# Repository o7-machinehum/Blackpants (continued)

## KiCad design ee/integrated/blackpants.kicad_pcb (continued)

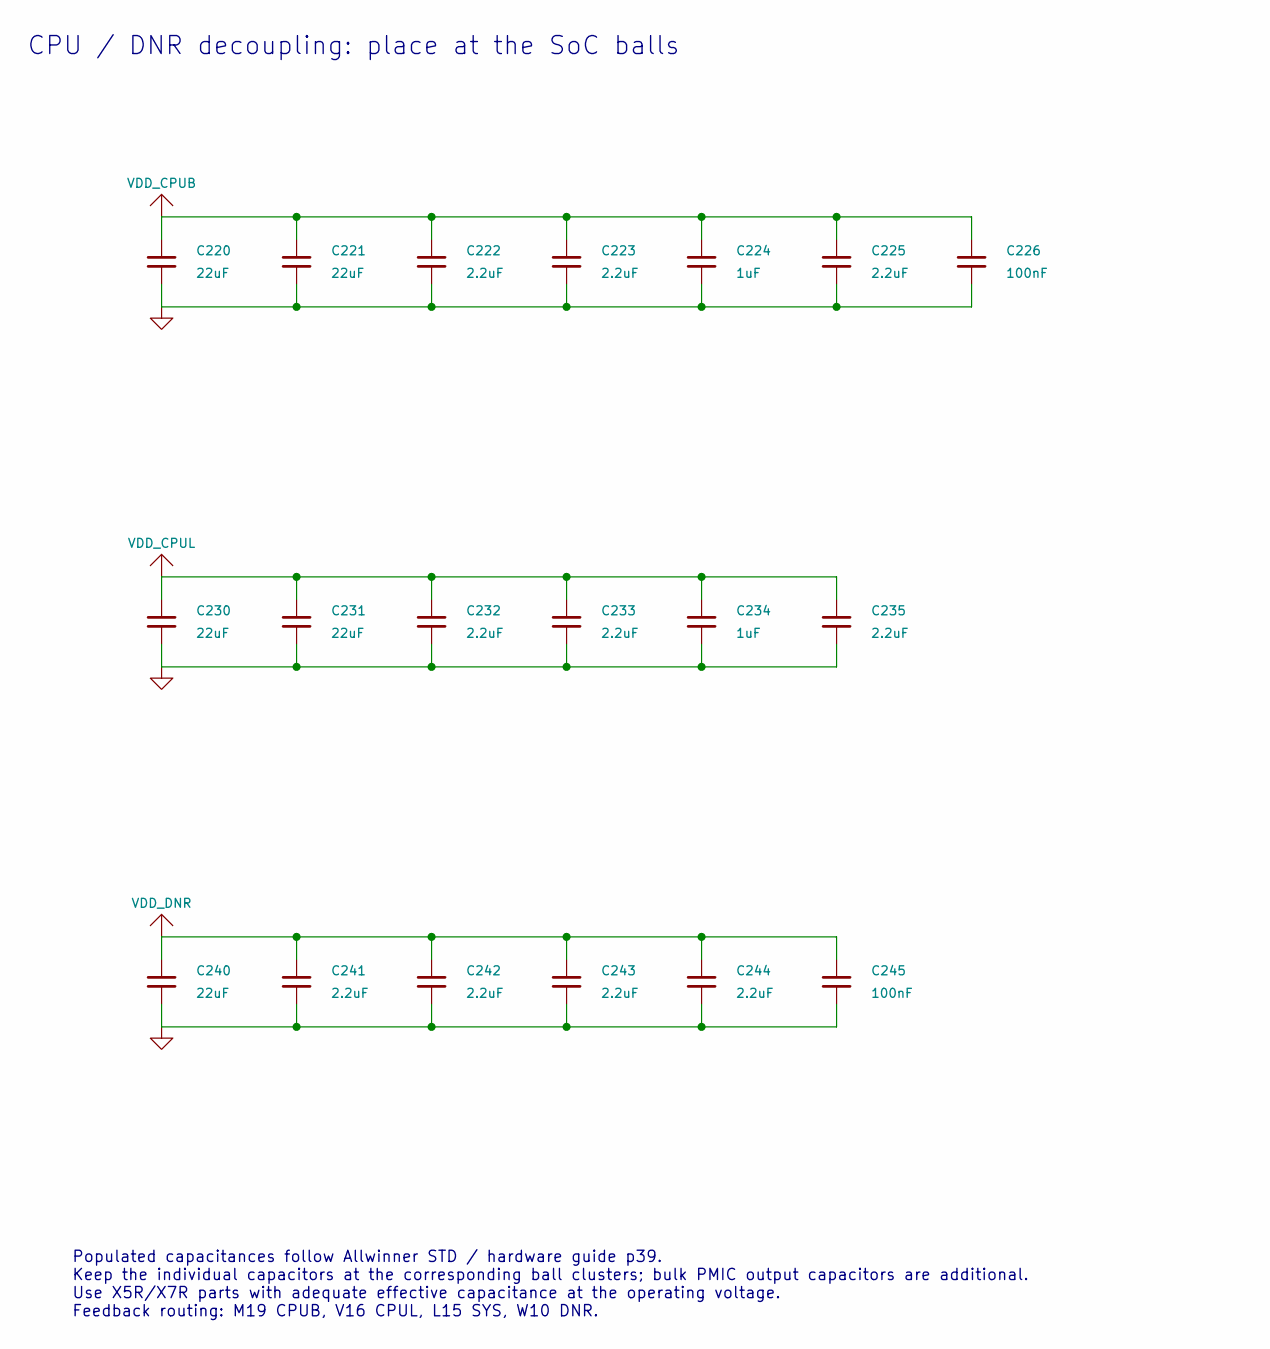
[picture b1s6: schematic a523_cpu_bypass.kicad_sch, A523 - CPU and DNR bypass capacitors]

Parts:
C220, C221, C230, C231, C240: 22uF; C_0402_1005Metric; Voltage 10V
C222, C223, C225, C232, C233, C235, C241, C242, C243, C244: 2.2uF; C_0402_1005Metric; Voltage 10V
C224, C234: 1uF; C_0402_1005Metric; Voltage 10V
C226, C245: 100nF; C_0201_0603Metric; Voltage 10V

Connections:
GND: C220.2, C221.2, C222.2, C223.2, C224.2, C225.2, C226.2, C230.2, C231.2, C232.2, C233.2, C234.2, C235.2, C240.2, C241.2, C242.2, C243.2, C244.2, C245.2; also elsewhere on the board
VDD_CPUB: C220.1, C221.1, C222.1, C223.1, C224.1, C225.1, C226.1; also elsewhere on the board
VDD_CPUL: C230.1, C231.1, C232.1, C233.1, C234.1, C235.1; also elsewhere on the board
VDD_DNR: C240.1, C241.1, C242.1, C243.1, C244.1, C245.1; also elsewhere on the board

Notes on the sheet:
CPU / DNR decoupling: place at the SoC balls
Populated capacitances follow Allwinner STD / hardware guide p39. Keep the individual capacitors at the corresponding ball clusters; bulk PMIC output capacitors are additional. Use X5R/X7R parts with adequate effective capacitance at the operating voltage. Feedback routing: M19 CPUB, V16 CPUL, L15 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

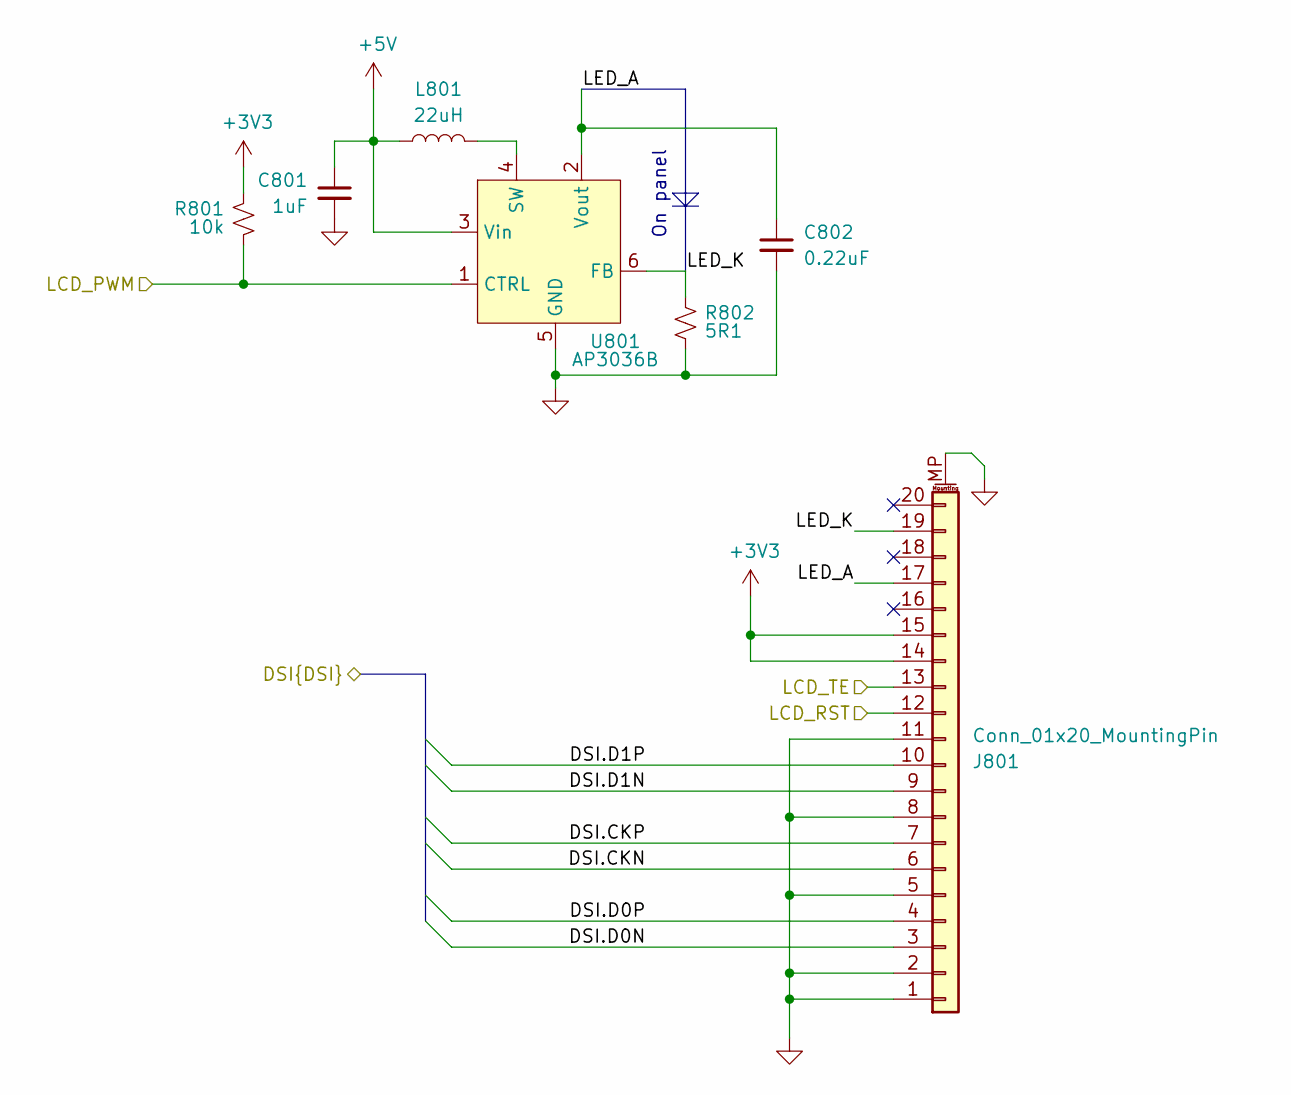
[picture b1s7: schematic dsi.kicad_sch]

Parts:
C801: 1uF; C_0402_1005Metric; MPN CL05A105KO5NNNC
C802: 0.22uF; C_0603_1608Metric; MPN CC0603KRX7R7BB224
J801: Conn_01x20_MountingPin; Hirose_FH12-20S-0.5SH_1x20-1MP_P0.50mm_Horizontal; MPN FH12-20S-0.5SH(55)
L801: 22uH; L_1210_3225Metric; MPN CBC3225T220MR
R801: 10k; R_0402_1005Metric; MPN RC0402JR-0710KL
R802: 5R1; R_0402_1005Metric; MPN RC0402JR-075R1L
U801: AP3036B; SOT-23-6; MPN AP3036BKTR-G1

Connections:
+3V3: J801.14, J801.15, R801.1; also elsewhere on the board
+5V: C801.1, L801.1, U801.3 (Vin); also elsewhere on the board
/A523 Display DSI/DSI.CKN: J801.6; also elsewhere on the board
/A523 Display DSI/DSI.CKP: J801.7; also elsewhere on the board
/A523 Display DSI/DSI.D0N: J801.3; also elsewhere on the board
/A523 Display DSI/DSI.D0P: J801.4; also elsewhere on the board
/A523 Display DSI/DSI.D1N: J801.9; also elsewhere on the board
/A523 Display DSI/DSI.D1P: J801.10; also elsewhere on the board
/Display / backlight/LED_A: C802.1, J801.17, U801.2 (Vout)
/Display / backlight/LED_K: J801.19, R802.1, U801.6 (FB)
/LCD_PWM: R801.2, U801.1 (CTRL); also elsewhere on the board
/LCD_RST: J801.12; also elsewhere on the board
/LCD_TE: J801.13; also elsewhere on the board
GND: C801.2, C802.2, J801.1, J801.2, J801.5, J801.8, J801.11, J801.MP (MountPin), R802.2, U801.5 (GND); also elsewhere on the board
unnamed: L801.2, U801.4 (SW)

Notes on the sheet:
On panel

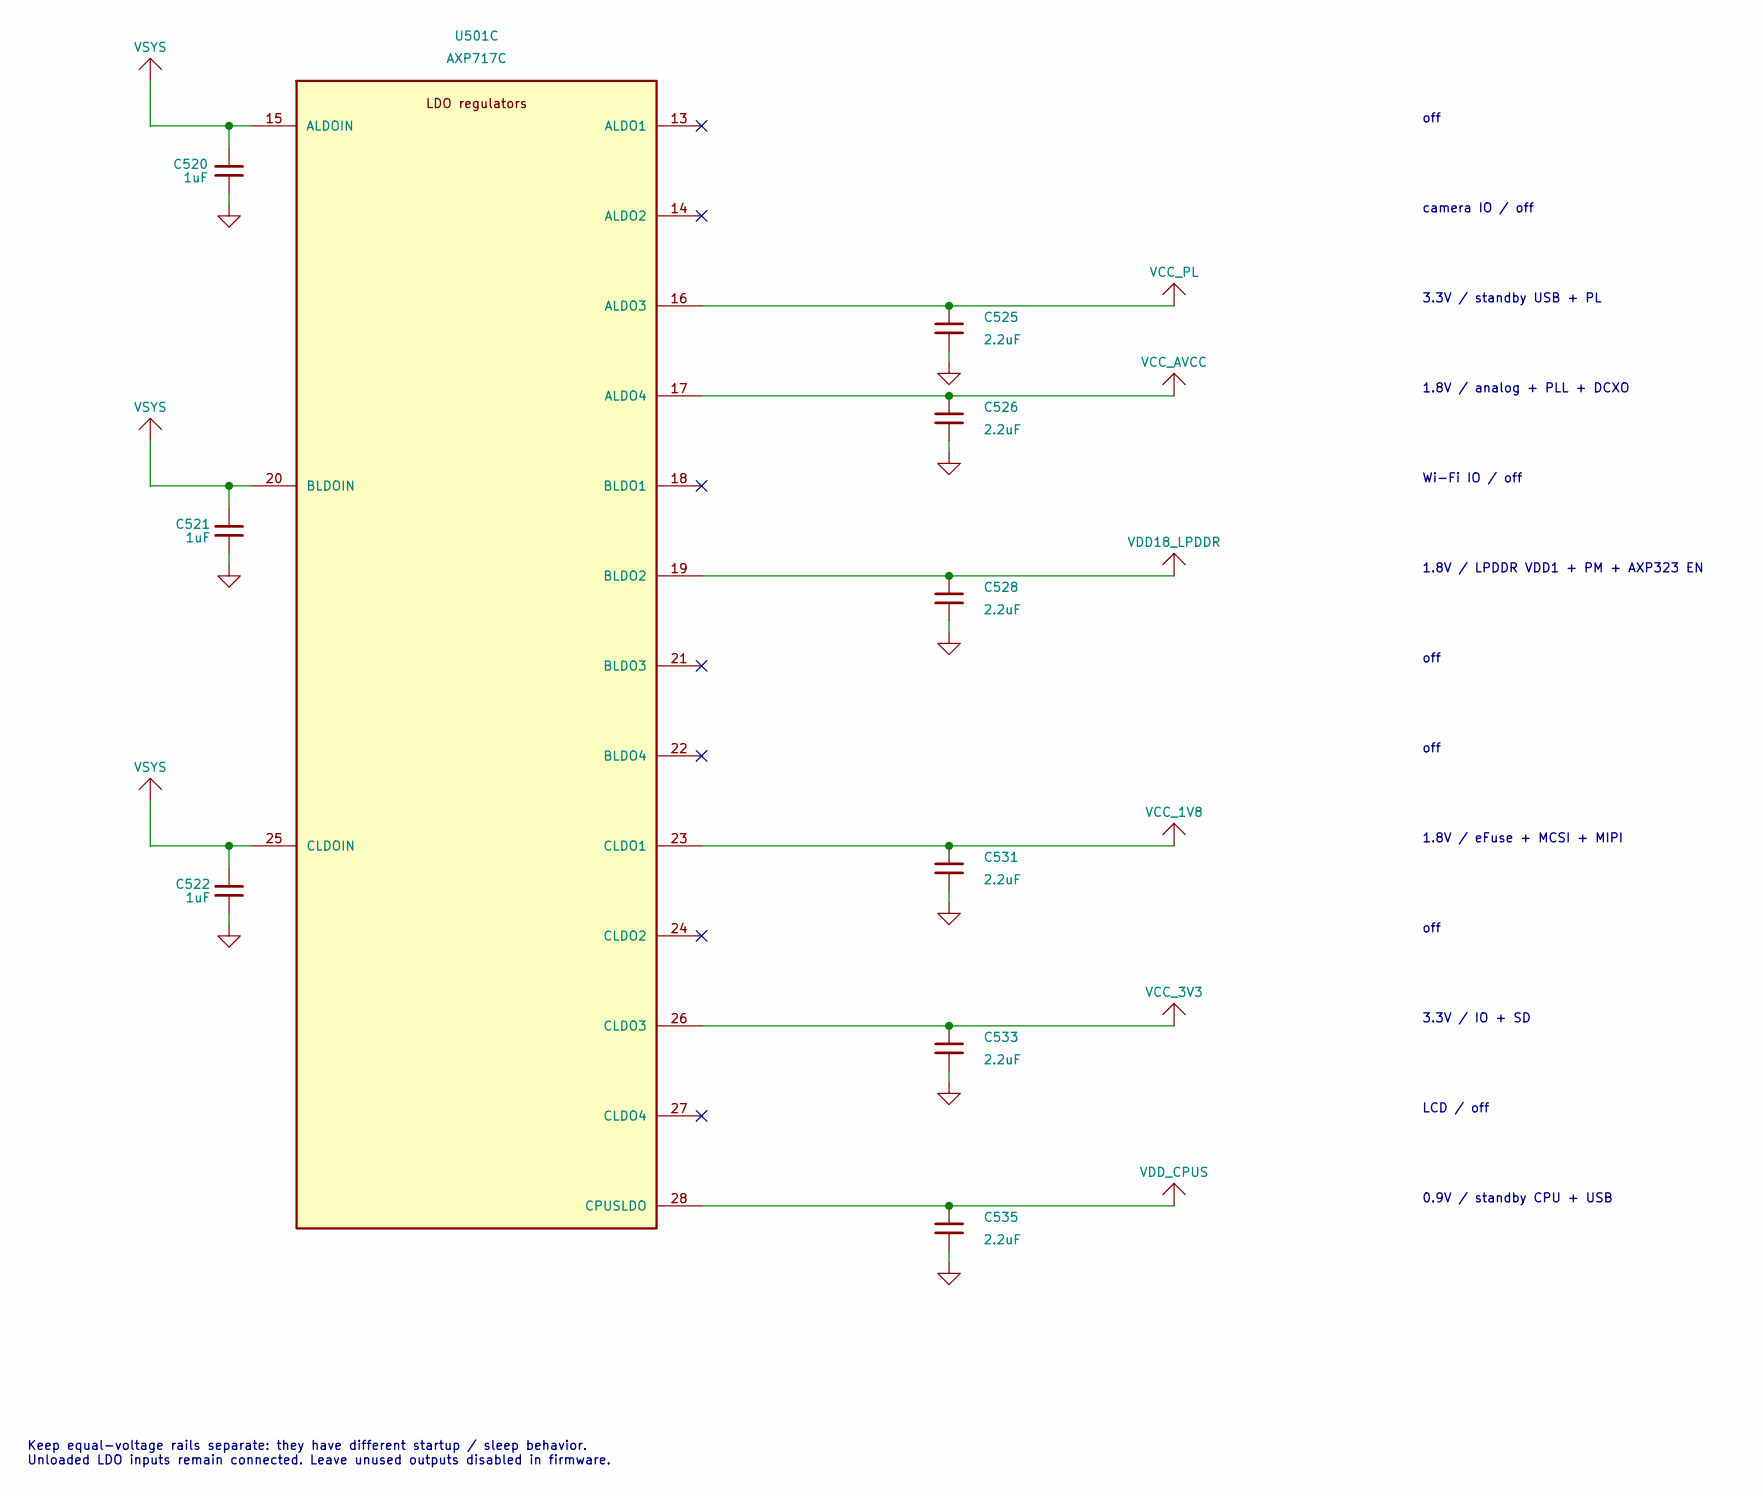
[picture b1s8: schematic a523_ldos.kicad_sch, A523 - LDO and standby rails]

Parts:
C520, C521, C522: 1uF; C_0402_1005Metric; Voltage 10V
C525, C526, C528, C531, C533, C535: 2.2uF; C_0402_1005Metric; Voltage 10V
U501: AXP717C; QFN-52-1EP_6x6mm_P0.4mm_EP4.6x4.6mm

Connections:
GND: C520.2, C521.2, C522.2, C525.2, C526.2, C528.2, C531.2, C533.2, C535.2; also elsewhere on the board
VCC_1V8: C531.1, U501.23 (CLDO1); also elsewhere on the board
VCC_3V3: C533.1, U501.26 (CLDO3); also elsewhere on the board
VCC_AVCC: C526.1, U501.17 (ALDO4); also elsewhere on the board
VCC_PL: C525.1, U501.16 (ALDO3); also elsewhere on the board
VDD18_LPDDR: C528.1, U501.19 (BLDO2); also elsewhere on the board
VDD_CPUS: C535.1, U501.28 (CPUSLDO); also elsewhere on the board
VSYS: C520.1, C521.1, C522.1, U501.15 (ALDOIN), U501.20 (BLDOIN), U501.25 (CLDOIN); also elsewhere on the board

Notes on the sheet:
3.3V / IO + SD
1.8V / eFuse + MCSI + MIPI
off
Keep equal-voltage rails separate: they have different startup / sleep behavior. Unloaded LDO inputs remain connected. Leave unused outputs disabled in firmware.
camera IO / off
1.8V / analog + PLL + DCXO
0.9V / standby CPU + USB
LCD / off
3.3V / standby USB + PL
Wi-Fi IO / off
1.8V / LPDDR VDD1 + PM + AXP323 EN

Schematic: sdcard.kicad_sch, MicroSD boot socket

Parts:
C102: 100nF; C_0402_1005Metric; Voltage 10V
C103: 22uF; C_0603_1608Metric; Voltage 10V
J105: microSD / boot; microSD_HC_Hirose_DM3AT-SF-PEJM5
R103: 10k; R_0402_1005Metric
R104, R105, R106, R107, R108: 100k; R_0402_1005Metric

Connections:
/A523 SD and GPIO/SD0.CLK: J105.5 (CLK); also elsewhere on the board
/A523 SD and GPIO/SD0.CMD: J105.3 (CMD), R103.2; also elsewhere on the board
/A523 SD and GPIO/SD0.D0: J105.7 (DAT0), R104.2; also elsewhere on the board
/A523 SD and GPIO/SD0.D1: J105.8 (DAT1), R105.2; also elsewhere on the board
/A523 SD and GPIO/SD0.D2: J105.1 (DAT2), R106.2; also elsewhere on the board
/A523 SD and GPIO/SD0.D3: J105.2 (DAT3/CD), R107.2; also elsewhere on the board
/A523 SD and GPIO/SD0.DET: J105.9 (DET_B), R108.2; also elsewhere on the board
GND: C102.2, C103.2, J105.6 (VSS), J105.10 (DET_A), J105.SH (SHIELD); also elsewhere on the board
VCC_3V3: C102.1, C103.1, J105.4 (VDD), R103.1, R104.1, R105.1, R106.1, R107.1, R108.1; also elsewhere on the board

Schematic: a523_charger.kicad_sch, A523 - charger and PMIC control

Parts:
C501, C505: 10uF; C_0603_1608Metric; Voltage 10V
C502, C503, C504: 22uF; C_0603_1608Metric; Voltage 10V
C506: 4.7uF; C_0402_1005Metric; Voltage 10V
C507, C510: 100nF; C_0402_1005Metric; Voltage 10V
C508, C509: 1uF; C_0402_1005Metric; Voltage 10V
L504: 1uH; L_Coilcraft_XAL4020-XXX; MPN XAL4020-102MEB
R501, R502: 2.2k; R_0402_1005Metric
R503: 10k; R_0402_1005Metric
R504: 10k; R_0402_1005Metric; not fitted
U501: AXP717C; QFN-52-1EP_6x6mm_P0.4mm_EP4.6x4.6mm

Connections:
/AP_NMI: R503.2, U501.37 (IRQ); also elsewhere on the board
/AP_RESET_N: R504.2, U501.1 (PWROK); also elsewhere on the board
/BAT_TS: U501.39 (TS); also elsewhere on the board
/CHGLED_N: U501.38 (CHGLED); also elsewhere on the board
/PMIC_CC1: U501.4 (CC1); also elsewhere on the board
/PMIC_CC2: U501.5 (CC2); also elsewhere on the board
/PMIC_USB_DM: U501.2 (DM); also elsewhere on the board
/PMIC_USB_DP: U501.3 (DP); also elsewhere on the board
/PMU.SCL: R501.2, U501.52 (SCK); also elsewhere on the board
/PMU.SDA: R502.2, U501.51 (SDA); also elsewhere on the board
/PWRON: C510.1, U501.6 (PWRON); also elsewhere on the board
GND: C501.2, C502.2, C503.2, C504.2, C505.2, C506.2, C507.2, C508.2, C509.2, C510.2, U501.8 (GND), U501.53 (EP); also elsewhere on the board
unnamed: L504.1, U501.45 (SW), U501.46 (SW)
unnamed: C508.1, U501.7 (VREF)
PMIC_VMID: C502.1, U501.47 (VMID), U501.48 (VMID)
VBAT: C506.1, C507.1, U501.41 (BAT), U501.42 (BAT); also elsewhere on the board
VBUS: C501.1, U501.49 (VBUS), U501.50 (VBUS); also elsewhere on the board
VCC_PL: R501.1, R502.1; also elsewhere on the board
VCC_RTC: C509.1, R503.1, R504.1, U501.35 (VRTC); also elsewhere on the board
VSYS: C503.1, C504.1, C505.1, L504.2, U501.43 (VSYS), U501.44 (VSYS); also elsewhere on the board

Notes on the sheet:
Single-cell Li-ion / 3.9-5.5V USB input A523 factory configuration required I2C: 0x34 (7-bit)
R504 is not fitted: retain the reference reset pull-up option. DP/DM sense resistors (470 ohm) belong at the USB interface. BAT_TS connects to the battery NTC; PWRON to the power key.
Do not bridge VMID to VBUS in the battery design. Place the charger input/output capacitors at U501.

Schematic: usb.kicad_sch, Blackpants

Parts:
C12: 4.7uF; C_0402_1005Metric; MPN CC0402MRX5R5BB475
C13, C14, C15, C16, C23, C27, C31: 100nF; C_0402_1005Metric; MPN CL05B104KB54PNC
C28, C29: 10pF; C_0402_1005Metric; MPN GRM1555C1H100FA01D
C30: 1uF; C_0402_1005Metric; MPN CL05B105KQ5NQNC
D8: LED; LED_0603_1608Metric; MPN KT-0603R
J4, J5: USB_A; USB_A_Receptacle_GCT_1; MPN USB1046-GF-0190-L-B-A
JP4, JP6: SolderJumper_2_Bridged; SolderJumper-2_P1.3mm_Bridged_Pad1.0x1.5mm
JP5: SolderJumper_3_Bridged12; SolderJumper-3_P1.3mm_Bridged2Bar12_RoundedPad1.0x1.5mm
R3, R4, R10: 5.1K; R_0402_1005Metric; MPN RC0402FR-135K1L
R5: 1M; R_0402_1005Metric; MPN RC0402FR-131ML
R6, R7, R9, R13, R27, R28: 100K; R_0402_1005Metric; MPN RC0402FR-13100KL
R8: 12K; R_0402_1005Metric; MPN RC0402FR-1312KL
R19: 1K; R_0402_1005Metric; MPN 0402WGF1001TCE
U3: USB2514B_Bi; QFN-36-1EP_6x6mm_P0.5mm_EP3.7x3.7mm; MPN USB2514BI-AEZG-TR
U4: MIC2026-1xM; SOIC-8_3.9x4.9mm_P1.27mm; MPN MIC2026-1YM-TR
U5, U6: USBLC6-2SC6; SOT-23-6; MPN USBLC6-2SC6
Y1: 24Mhz; Crystal_SMD_Citizen_CS325S-4Pin_3.2x2.5mm; MPN CS325S24000000ABJT

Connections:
+3V3: C12.1, C13.1, C14.1, C15.1, C16.1, JP4.2 (B), JP5.3 (B), JP6.2 (B), R9.1, R27.1, R28.1, U3.5 (VDDA33), U3.8 (USBDM_DN4/PRT_DIS_M4), U3.9 (USBDP_DN4/PRT_DIS_P4), U3.10 (VDDA33), U3.15 (VDD33), U3.23 (VDD33), U3.29 (VDDA33), U3.36 (VDDA33); also elsewhere on the board
+5V: C30.2, R6.1, U4.7 (IN); also elsewhere on the board
/A523 USB PHY/USB_HOST.DM: U3.30 (USBDM_UP); also elsewhere on the board
/A523 USB PHY/USB_HOST.DP: U3.31 (USBDP_UP); also elsewhere on the board
/STM32 + Keyboard/I2C.SCL: R3.2, U3.24 (SCL/SMBCLK/CFG_SEL0); also elsewhere on the board
/STM32 + Keyboard/I2C.SDA: R4.2, U3.22 (SDA/SMBDATA/NON_REM1); also elsewhere on the board
/USB3.D+: U3.4 (USBDP_DN2/PRT_DIS_P2); also elsewhere on the board
/USB3.D-: U3.3 (USBDM_DN2/PRT_DIS_M2); also elsewhere on the board
/USB Hub/HS_IND: R10.2, U3.25 (HS_IND/CFG_SEL1)
/USB Hub/SUSP_IND: R13.1, R19.2, U3.28 (SUSP_IND/LOCAL_PWR/NON_REM0)
/USB Hub/USB1.D+: U3.2 (USBDP_DN1/PRT_DIS_P1), U6.1 (I/O1)
/USB Hub/USB1.D-: U3.1 (USBDM_DN1/PRT_DIS_M1), U6.3 (I/O2)
/USB Hub/USB2.D+: U3.7 (USBDP_DN3/PRT_DIS_P3), U5.1 (I/O1)
/USB Hub/USB2.D-: U3.6 (USBDM_DN3/PRT_DIS_M3), U5.3 (I/O2)
/USB Hub/~RESET: C31.2, R9.2, U3.26 (RESET_N)
GND: C12.2, C13.2, C14.2, C15.2, C16.2, C23.2, C27.2, C28.1, C29.1, C30.1, C31.1, D8.1 (K), J4.4 (GND), J4.5 (Shield), J5.4 (GND), J5.5 (Shield), JP5.1 (A), R7.2, R8.2, R13.2, U3.11 (TEST), U3.37 (VSS), U4.6 (GND), U5.2 (GND), U6.2 (GND), Y1.2, Y1.4; also elsewhere on the board
unnamed: D8.2 (A), R19.1
unnamed: J4.3 (D+), U6.6 (I/O1)
unnamed: J4.2 (D-), U6.4 (I/O2)
unnamed: J4.1 (VBUS), U4.8 (OUTA), U6.5 (VBUS)
unnamed: J5.3 (D+), U5.6 (I/O1)
unnamed: J5.2 (D-), U5.4 (I/O2)
unnamed: J5.1 (VBUS), U4.5 (OUTB), U5.5 (VBUS)
unnamed: JP4.1 (A), U3.17 (OCS_N2)
unnamed: JP5.2 (C), R3.1, R4.1, R10.1
unnamed: JP6.1 (A), U3.21 (OCS_N4)
unnamed: C27.1, U3.14 (CRFILT)
unnamed: R27.2, U3.13 (OCS_N1), U4.2 (FLGA)
unnamed: R28.2, U3.19 (OCS_N3), U4.3 (FLGB)
unnamed: C23.1, U3.34 (PLLFILT)
unnamed: U3.12 (PRTPWR1/BC_EN1), U4.1 (ENA)
unnamed: U3.18 (PRTPWR3/BC_EN3), U4.4 (ENB)
unnamed: R8.1, U3.35 (RBIAS)
unnamed: R6.2, R7.1, U3.27 (VBUS_DET)
unnamed: C28.2, R5.1, U3.33 (XTALIN/CLKIN), Y1.3
unnamed: C29.2, R5.2, U3.32 (XTALOUT), Y1.1

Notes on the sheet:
USB-A Probes These touch the blackhat

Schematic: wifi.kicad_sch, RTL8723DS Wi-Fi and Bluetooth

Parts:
C701, C702: DNP; C_0402_1005Metric; Voltage 10V; not fitted
C703: 10uF; C_0603_1608Metric; Voltage 10V
C704, C705: 100nF; C_0402_1005Metric; Voltage 10V
J701: Antenna; SMA_Amphenol_901-143_Horizontal
L701: 120R @100MHz / >=0.6A; L_0603_1608Metric
R703: 0; R_0402_1005Metric
R710, R711, R712, R713, R714: 10k; R_0201_0603Metric
R715: 10k; R_0402_1005Metric
R716, R717, R718: 100k; R_0402_1005Metric
U701: RTL8723DS; RTL8723

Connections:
+3V3: C705.1, L701.1, R710.1, R711.1, R712.1, R713.1, R714.1, R715.1, U701.22 (VDD_IO); also elsewhere on the board
/A523 Wifi and BT/BT.RX: U701.42 (UART_TXD); also elsewhere on the board
/A523 Wifi and BT/BT.TX: U701.43 (UART_RXD); also elsewhere on the board
/A523 Wifi and BT/BT.~CTS: U701.41 (UART_RTS_N); also elsewhere on the board
/A523 Wifi and BT/BT.~RTS: U701.44 (UART_CTS_N); also elsewhere on the board
/A523 Wifi and BT/SD1.CLK: U701.17 (SD_CLK); also elsewhere on the board
/A523 Wifi and BT/SD1.CMD: R710.2, U701.16 (SD_CMD); also elsewhere on the board
/A523 Wifi and BT/SD1.D0: R711.2, U701.18 (SD_D0); also elsewhere on the board
/A523 Wifi and BT/SD1.D1: R712.2, U701.19 (SD_D1); also elsewhere on the board
/A523 Wifi and BT/SD1.D2: R713.2, U701.14 (SD_D2); also elsewhere on the board
/A523 Wifi and BT/SD1.D3: R714.2, U701.15 (SD_D3); also elsewhere on the board
/BT_HOST_WAKE: U701.7 (BT_HOST_WAKE); also elsewhere on the board
/BT_RESET_N: R717.1, U701.34 (BT_RST_N); also elsewhere on the board
/BT_WAKE: R718.1, U701.6 (BT_WAKE); also elsewhere on the board
/RTL8723DS/CLK32K: R715.2
/RTL8723DS/RF_ANT: C701.1, R703.1, U701.2 (WIFI/BT_ANT)
/WL_HOST_WAKE: U701.13 (WL_HOST_WAKE); also elsewhere on the board
/WL_REG_ON: R716.1, U701.12 (WL_REG_ON); also elsewhere on the board
GND: C701.2, C702.2, C703.2, C704.2, C705.2, J701.2 (Ext), R716.2, R717.2, R718.2, U701.1 (GND), U701.3 (GND), U701.20 (GND), U701.31 (GND), U701.33 (GND), U701.36 (GND); also elsewhere on the board
unnamed: C702.1, J701.1 (In), R703.2
VCC_WIFI: C703.1, C704.1, L701.2, U701.9 (VBAT)

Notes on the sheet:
Program BLDO1 = 3.3V before enabling PG / PH outputs. VBAT is filtered +3V3; VDD_IO is the separately sequenced VCC_PG. Module TX/RTS -> SoC RX/CTS; module RX/CTS <- SoC TX/RTS. X32KFOUT is open drain; R715 pulls it up to VCC_PG.

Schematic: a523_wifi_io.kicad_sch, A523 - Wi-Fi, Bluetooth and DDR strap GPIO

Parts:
C266: 100nF; C_0201_0603Metric; Voltage 10V
R204, R205: 1k; R_0402_1005Metric
R206, R207: 47k; R_0402_1005Metric; not fitted
R208: 33; R_0402_1005Metric
U201: A523; Allwinner_A523_FCCSP-522_15x15mm_P0.5mm

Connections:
+3V3: C266.1, U201.N6 (VCC-PG); also elsewhere on the board
/A523 Wifi and BT/BT.RX: U201.R5 (PG6); also elsewhere on the board
/A523 Wifi and BT/BT.TX: U201.U3 (PG7); also elsewhere on the board
/A523 Wifi and BT/BT.~CTS: U201.R4 (PG8); also elsewhere on the board
/A523 Wifi and BT/BT.~RTS: U201.U4 (PG9); also elsewhere on the board
/A523 Wifi and BT/DDR_ID0: R204.1, R206.2, U201.A5 (PH16)
/A523 Wifi and BT/DDR_ID1: R205.1, R207.2, U201.B5 (PH17)
/A523 Wifi and BT/SD1.CLK: R208.1; also elsewhere on the board
/A523 Wifi and BT/SD1.CMD: U201.R2 (PG1); also elsewhere on the board
/A523 Wifi and BT/SD1.D0: U201.P3 (PG2); also elsewhere on the board
/A523 Wifi and BT/SD1.D1: U201.P2 (PG3); also elsewhere on the board
/A523 Wifi and BT/SD1.D2: U201.T3 (PG4); also elsewhere on the board
/A523 Wifi and BT/SD1.D3: U201.T2 (PG5); also elsewhere on the board
/BT_HOST_WAKE: U201.A10 (PH4); also elsewhere on the board
/BT_RESET_N: U201.D10 (PH2); also elsewhere on the board
/BT_WAKE: U201.B10 (PH3); also elsewhere on the board
/WL_HOST_WAKE: U201.E10 (PH1); also elsewhere on the board
/WL_REG_ON: U201.F10 (PH0); also elsewhere on the board
GND: C266.2, R204.2, R205.2; also elsewhere on the board
unnamed: R208.2, U201.R1 (PG0)
VCC_3V3: R206.1, R207.1; also elsewhere on the board

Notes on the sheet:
SDIO1 / UART1 / DDR parameter straps
SDIO and UART use PG mux 2. PG voltage must match the module VDD_IO. Wi-Fi/BT control pins use PH (3.3V VCC_IO); the 1.8V PM bank is not used for these controls. PH16/PH17 = 0/0, GPADC1 selects DDR parameter set 1 (see analog page). Firmware must populate that parameter set for NT6AN512T32AV-J2.

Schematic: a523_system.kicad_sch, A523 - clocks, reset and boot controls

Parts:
C250, C251: 18pF; C_0402_1005Metric; Voltage 10V
C254, C255, C257: 100nF; C_0201_0603Metric; Voltage 10V
C256: 2.2uF; C_0402_1005Metric; Voltage 10V
C258, C259, C260: 1nF; C_0402_1005Metric; Voltage 10V
R201: 0; R_0402_1005Metric
U201: A523; Allwinner_A523_FCCSP-522_15x15mm_P0.5mm
Y201: 24MHz / CL20pF / 20ppm; Crystal_SMD_3225-4Pin_3.2x2.5mm

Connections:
/A523 Clocks/DXIN: C250.1, U201.AH13 (DXIN), Y201.1
/A523 Clocks/DXOUT: R201.2, U201.AJ13 (DXOUT)
/AP_NMI: C258.1, U201.AD11 (NMI); also elsewhere on the board
/AP_RESET_N: C259.1, U201.AC11 (RESET); also elsewhere on the board
/FEL_N: C260.1, U201.E12 (FEL); also elsewhere on the board
GND: C250.2, C251.2, C254.2, C255.2, C256.2, C257.2, C258.2, C259.2, C260.2, U201.AE13 (WREQIN), Y201.2 (G), Y201.4 (G); also elsewhere on the board
unnamed: C251.1, R201.1, Y201.3
VCC_1V8: C254.1, U201.N23 (VCC-EFUSE); also elsewhere on the board
VCC_AVCC: C256.1, C257.1, U201.AA12 (VCC-DCXO), U201.AB13 (VCC-PLL); also elsewhere on the board
VCC_RTC: C255.1, U201.AA10 (VCC-RTC); also elsewhere on the board

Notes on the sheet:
TEST / JTAG-SEL / PLLTEST / REFCLK-OUT: unconnected. WREQIN grounded; no Allwinner Wi-Fi clock fanout. C258/C259: 1nF NMI / reset filters. Tune crystal capacitors for CL and PCB stray capacitance.
System clocks / reset / FEL

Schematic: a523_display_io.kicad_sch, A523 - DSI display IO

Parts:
C262: 10uF; C_0402_1005Metric; Voltage 10V
C263, C264, C265: 100nF; C_0201_0603Metric; Voltage 10V
U201: A523; Allwinner_A523_FCCSP-522_15x15mm_P0.5mm

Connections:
+3V3: C265.1, U201.J6 (VCC-PE); also elsewhere on the board
/A523 Display DSI/DSI.CKN: U201.B26 (PD5); also elsewhere on the board
/A523 Display DSI/DSI.CKP: U201.A26 (PD4); also elsewhere on the board
/A523 Display DSI/DSI.D0N: U201.B24 (PD1); also elsewhere on the board
/A523 Display DSI/DSI.D0P: U201.A24 (PD0); also elsewhere on the board
/A523 Display DSI/DSI.D1N: U201.B25 (PD3); also elsewhere on the board
/A523 Display DSI/DSI.D1P: U201.A25 (PD2); also elsewhere on the board
GND: C262.2, C263.2, C264.2, C265.2; also elsewhere on the board
VCC_1V8: C264.1, U201.K21 (VCC-LVDS0); also elsewhere on the board
VCC_3V3: C262.1, C263.1, U201.J23 (VCC-PD); also elsewhere on the board

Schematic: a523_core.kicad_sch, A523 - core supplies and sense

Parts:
C201, C206, C207, C210, C211, C212: 2.2uF; C_0402_1005Metric; Voltage 10V
C202, C204, C209: 100nF; C_0201_0603Metric; Voltage 10V
C203: 1uF; C_0402_1005Metric; Voltage 10V
C205, C208: 22uF; C_0402_1005Metric; Voltage 10V
U201: A523; Allwinner_A523_FCCSP-522_15x15mm_P0.5mm

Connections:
/VDD_CPUB_FB: U201.M19 (VDD-CPUBFB); also elsewhere on the board
/VDD_CPUL_FB: U201.V16 (VDD-CPULFB); also elsewhere on the board
/VDD_DNR_FB: U201.W10 (VDD-DNRFB); also elsewhere on the board
/VDD_SYS_FB: U201.L15 (VDD-SYSFB); also elsewhere on the board
GND: C201.2, C202.2, C203.2, C204.2, C205.2, C206.2, C207.2, C208.2, C209.2, C210.2, C211.2, C212.2; also elsewhere on the board
VCC_3V3: C203.1, C204.1, U201.J12 (VCC-IO); also elsewhere on the board
VDD_CPUB: U201.N16 (VDD-CPUB), U201.N18 (VDD-CPUB), U201.N19 (VDD-CPUB), U201.P15 (VDD-CPUB), U201.P16 (VDD-CPUB), U201.P18 (VDD-CPUB), U201.P19 (VDD-CPUB); also elsewhere on the board
VDD_CPUL: U201.T16 (VDD-CPUL), U201.T18 (VDD-CPUL), U201.U16 (VDD-CPUL), U201.U18 (VDD-CPUL); also elsewhere on the board
VDD_CPUS: C201.1, C202.1, U201.Y12 (VDD-CPUS); also elsewhere on the board
VDD_DNR: U201.U9 (VDD-DNR), U201.U10 (VDD-DNR), U201.V9 (VDD-DNR), U201.V10 (VDD-DNR); also elsewhere on the board
VDD_SYS: C205.1, C206.1, C207.1, C208.1, C209.1, C210.1, C211.1, C212.1, U201.K10 (VDD-VE), U201.K19 (VDD-DE), U201.L10 (VDD-VE), U201.L18 (VDD-DE), U201.L19 (VDD-DE), U201.M12 (VDD-SYS), U201.M14 (VDD-SYS), U201.M15 (VDD-SYS), U201.N8 (VDD-GPU), U201.N10 (VDD-GPU), U201.P9 (VDD-GPU), U201.P10 (VDD-GPU); also elsewhere on the board

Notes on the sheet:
At GPU balls N8/N10/P9/P10
A523 core power and remote sense
Sense pins are dedicated internal supply taps. Route directly to PMIC feedback. CPU / DNR bypass is on the next page.
At DE balls K19/L18/L19
At VE balls K10/L10

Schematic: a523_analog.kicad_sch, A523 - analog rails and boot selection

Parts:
C273, C274, C275, C276: 470nF; C_0402_1005Metric; Voltage 10V
C277, C278, C279, C280, C281, C284: 2.2uF; C_0402_1005Metric; Voltage 10V
C283: 100nF; C_0201_0603Metric; Voltage 10V
R211, R213: 10k / 1%; R_0402_1005Metric
R212: 3.9k / 1%; R_0402_1005Metric
R214: 2.7k / 1%; R_0402_1005Metric
U201: A523; Allwinner_A523_FCCSP-522_15x15mm_P0.5mm

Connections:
/A523 Analog straps/ALDO_OUT: C277.1, U201.AE3 (ALDO-OUT)
/A523 Analog straps/BOOT_ADC: R211.2, R212.1, U201.W2 (GPADC0)
/A523 Analog straps/CPVDD: C279.1, U201.AE5 (CPVDD)
/A523 Analog straps/CPVEE: C278.1, U201.AC5 (CPVEE), U201.AE4 (VEE)
/A523 Analog straps/DDR_ADC: R213.2, R214.1, U201.W3 (GPADC1)
/A523 Analog straps/VCM_ADC: C276.1, U201.U6 (VCM-ADC)
/A523 Analog straps/VRA1: C273.1, U201.AC4 (VRA1)
/A523 Analog straps/VRA2: C274.1, U201.AC3 (VRA2)
/A523 Analog straps/VRP: C275.1, U201.AA4 (VRP)
GND: C273.2, C274.2, C275.2, C276.2, C277.2, C278.2, C279.2, C280.2, C281.2, C283.2, C284.2, R212.2, R214.2, U201.AA3 (AGND), U201.U7 (VREFN-ADC); also elsewhere on the board
VCC_1V8: C281.1, U201.AG3 (CPVIN); also elsewhere on the board
VCC_3V3: C283.1, U201.AA5 (VDD33); also elsewhere on the board
VCC_AVCC: C280.1, C284.1, R211.1, R213.1, U201.W6 (VREFP-ADC), U201.W7 (AVCC); also elsewhere on the board

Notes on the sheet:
Analog support / boot and DRAM ID straps
BOOT_ADC: STD 10k / 3.9k, SD boot available. DDR_ADC: 0.383V; PH16/PH17 = 0/0 selects set 1. Build set 1 for Nanya 16Gb LPDDR4. Unused audio / ADC IO is unconnected. Keep audio and headphone blocks disabled.

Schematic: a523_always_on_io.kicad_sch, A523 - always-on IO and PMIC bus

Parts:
C267, C268, C269, C270: 100nF; C_0201_0603Metric; Voltage 10V
U201: A523; Allwinner_A523_FCCSP-522_15x15mm_P0.5mm

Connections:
/PMU.SCL: U201.AJ7 (PL0); also elsewhere on the board
/PMU.SDA: U201.AH7 (PL1); also elsewhere on the board
GND: C267.2, C268.2, C269.2, C270.2; also elsewhere on the board
VCC_1V8: C269.1, C270.1, U201.H10 (VCC-MCSI), U201.J7 (VCC-PK); also elsewhere on the board
VCC_PL: C267.1, U201.AA9 (VCC-PL); also elsewhere on the board
VDD18_LPDDR: C268.1, U201.AC7 (VCC-PM); also elsewhere on the board

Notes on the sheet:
PMIC control bus and standby IO
PL0 / PL1: S-TWI0 mux 2, 3.3V. PMIC addresses: 0x34 and 0x36. MCSI must be supplied for SD voltage switching. PK: unused, supplied at 1.8V. PM: 1.8V standby; GPIOs unused.

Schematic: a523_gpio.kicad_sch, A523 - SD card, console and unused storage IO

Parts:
C261: 100nF; C_0201_0603Metric; Voltage 10V
R203: 33; R_0402_1005Metric
U201: A523; Allwinner_A523_FCCSP-522_15x15mm_P0.5mm

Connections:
/A523 SD and GPIO/SD0.CLK: R203.2; also elsewhere on the board
/A523 SD and GPIO/SD0.CMD: U201.A12 (PF3); also elsewhere on the board
/A523 SD and GPIO/SD0.D0: U201.B13 (PF1); also elsewhere on the board
/A523 SD and GPIO/SD0.D1: U201.C13 (PF0); also elsewhere on the board
/A523 SD and GPIO/SD0.D2: U201.B11 (PF5); also elsewhere on the board
/A523 SD and GPIO/SD0.D3: U201.C11 (PF4); also elsewhere on the board
/A523 SD and GPIO/SD0.DET: U201.C12 (PF6); also elsewhere on the board
/LCD_PWM: U201.K28 (PB8); also elsewhere on the board
/LCD_RST: U201.K27 (PB7); also elsewhere on the board
/LCD_TE: U201.J29 (PB6); also elsewhere on the board
/UART0_RX: U201.L25 (PB10)
/UART0_TX: U201.L24 (PB9)
/USB0_VBUS_DET: U201.L26 (PB11); also elsewhere on the board
GND: C261.2; also elsewhere on the board
unnamed: R203.1, U201.B12 (PF2)
VCC_3V3: C261.1, U201.N22 (VCC-PC); also elsewhere on the board

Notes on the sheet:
Boot SD / UART0 console / GPIO
UART0: PB9 / PB10, mux 2. SDC0: PF0..PF5, mux 2; PF6 detect. LCD PWM: PB8 mux 6. Reset / TE: GPIO. PB11: divided USB0 VBUS detect. I2C1: expansion header with 3.3V pull-ups.

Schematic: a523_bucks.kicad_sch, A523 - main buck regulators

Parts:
C511, C512, C513: 1uF; C_0402_1005Metric; Voltage 10V
C514, C515, C516: 22uF; C_0603_1608Metric; Voltage 10V
C517: 4.7uF; C_0402_1005Metric; Voltage 10V
L501, L502, L503: 1uH; L_Coilcraft_XAL4020-XXX; Rating Check peak/RMS current and DC bias at s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; MPN XAL4020-102MEB
U501: AXP717C; QFN-52-1EP_6x6mm_P0.4mm_EP4.6x4.6mm

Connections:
/VCC_DRAM_FB: U501.29 (FB3); also elsewhere on the board
/VDD_CPUL_FB: U501.12 (FB1); also elsewhere on the board
/VDD_SYS_FB: U501.34 (FB2); also elsewhere on the board
GND: C511.2, C512.2, C513.2, C514.2, C515.2, C516.2, C517.2; also elsewhere on the board
unnamed: L501.1, U501.10 (LX1), U501.11 (LX1)
unnamed: L502.1, U501.33 (LX2)
unnamed: L503.1, U501.30 (LX3)
VCC_DRAM: C516.1, L503.2; also elsewhere on the board
VDD_CPUL: C514.1, L501.2; also elsewhere on the board
VDD_SYS: C515.1, C517.1, L502.2; also elsewhere on the board
VSYS: C511.1, C512.1, C513.1, U501.9 (VIN1), U501.31 (VIN3), U501.32 (VIN2); also elsewhere on the board

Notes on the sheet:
FB3 also supplies CPUSLDO: allow at least 30mA. Do not pick up feedback at the inductor output. Keep each VIN bypass capacitor close to its pin. Inductors: 1uH, DCR < 100mOhm; check saturation margin.
Remote feedback
FB1 -> SoC VDD-CPULFB (V16) FB2 -> SoC VDD-SYSFB (L15) FB3 -> VCC_DRAM at the load, through NT301
1.1V / LPDDR4 1.5A converter
0.9V 3A converter
0.9V default / DVFS 4A converter

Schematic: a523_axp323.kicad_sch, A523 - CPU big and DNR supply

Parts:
C540, C541, C542, C549, C550, C551: 2.2uF; C_0402_1005Metric; Voltage 10V
C543, C544, C545: 10uF; C_0603_1608Metric; Voltage 10V
C552: 1uF; C_0402_1005Metric; Voltage 10V
L505, L506, L507: 1uH; L_Coilcraft_XAL4020-XXX; Rating Check peak/RMS current and DC bias at s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; MPN XAL4020-102MEB
U502: AXP323; QFN-20-1EP_3x3mm_P0.4mm_EP1.65x1.65mm

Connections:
/AP_RESET_N: U502.13 (PWROK); also elsewhere on the board
/PMU.SCL: U502.6 (SCL); also elsewhere on the board
/PMU.SDA: U502.5 (SDA); also elsewhere on the board
/VDD_CPUB_FB: U502.1 (DCDC2), U502.16 (DCDC1); also elsewhere on the board
/VDD_DNR_FB: U502.4 (DCDC3); also elsewhere on the board
GND: C540.2, C541.2, C542.2, C543.2, C544.2, C545.2, C549.2, C550.2, C551.2, C552.2, U502.9 (GND), U502.21 (EP); also elsewhere on the board
unnamed: C549.1, U502.15 (ALDO1)
unnamed: C550.1, U502.12 (DLDO1)
unnamed: L505.1, U502.18 (LX1)
unnamed: L506.1, U502.19 (LX2)
unnamed: L507.1, U502.3 (LX3)
unnamed: C551.1, U502.7 (RTCLDO)
unnamed: C552.1, U502.8 (VREF)
VDD18_LPDDR: U502.14 (PWRON); also elsewhere on the board
VDD_CPUB: C543.1, C544.1, L505.2, L506.2; also elsewhere on the board
VDD_DNR: C545.1, L507.2; also elsewhere on the board
VSYS: C540.1, C541.1, C542.1, U502.2 (VIN3), U502.17 (VIN1), U502.20 (VIN2); also elsewhere on the board

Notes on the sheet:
DCDC1 + DCDC2 Factory parallel mode 0.9V default / DVFS
DCDC3: 0.9V
I2C: 0x36 (7-bit) PWRON factory mode: EN PWROK joins the reset net. IRQ and spare LDO loads unused.
Both CPU feedback inputs return from A523 M19. DNR feedback returns from W10. Use matched L505/L506. Place C540 directly at VIN1. BLDO2 enables AXP323; AXP717C DCDCEN is unused in this reference configuration.

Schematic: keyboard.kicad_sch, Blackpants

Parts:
SW11: SW_Push; SW_Push_1P1T_NO_CK_KSC7xxJ
SW12, SW13, SW14, SW15, SW16, SW17, SW18, SW19: SW_Push; SW_Push_1P1T_NO_CK_KSC7xxJ; not fitted
U14: keyboard_arturo182

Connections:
/STM32 + Keyboard/Keyboard/COL_0: SW11.1, U14.1 (ESC), U14.17 (`), U14.43 (TAB), U14.69 (FN), U14.95 (SHL), U14.121 (CTRL), U14.137 (<); also elsewhere on the board
/STM32 + Keyboard/Keyboard/COL_1: SW12.1, U14.3 (F1), U14.19 (1), U14.45 (Q), U14.71 (A), U14.97 (Z), U14.123 (MT), U14.139 (\/); also elsewhere on the board
/STM32 + Keyboard/Keyboard/COL_2: SW13.1, U14.5 (F2), U14.21 (2), U14.47 (W), U14.73 (S), U14.99 (X), U14.125 (ALT), U14.141 (>); also elsewhere on the board
/STM32 + Keyboard/Keyboard/COL_3: SW14.1, U14.7 (F3), U14.23 (3), U14.49 (E), U14.75 (D), U14.101 (C), U14.115 (/), U14.127 (\); also elsewhere on the board
/STM32 + Keyboard/Keyboard/COL_4: SW15.1, U14.9 (F4), U14.25 (4), U14.51 (R), U14.77 (F), U14.103 (V), U14.117 (/\), U14.129 (SP); also elsewhere on the board
/STM32 + Keyboard/Keyboard/COL_5: SW16.1, U14.11 (F5), U14.27 (5), U14.53 (T), U14.79 (G), U14.105 (B), U14.119 (SHR), U14.131 (SP); also elsewhere on the board
/STM32 + Keyboard/Keyboard/COL_6: SW17.1, U14.13 (F6), U14.29 (6), U14.55 (Y), U14.81 (H), U14.89 (;), U14.107 (N), U14.133 (SP); also elsewhere on the board
/STM32 + Keyboard/Keyboard/COL_7: SW18.1, U14.15 (BS), U14.31 (7), U14.57 (U), U14.83 (J), U14.91 ('), U14.109 (M), U14.135 (AGR); also elsewhere on the board
/STM32 + Keyboard/Keyboard/COL_8: SW19.1, U14.33 (8), U14.37 (0), U14.59 (I), U14.63, U14.85 (K), U14.93 (RET), U14.111 (,); also elsewhere on the board
/STM32 + Keyboard/Keyboard/COL_9: U14.35 (9), U14.39 (-), U14.41 (=), U14.61 (O), U14.65 ([), U14.67 (]), U14.87 (L), U14.113 (.); also elsewhere on the board
/STM32 + Keyboard/Keyboard/ROW_0: U14.2, U14.4, U14.6, U14.8, U14.10, U14.12, U14.14, U14.16, U14.38, U14.40; also elsewhere on the board
/STM32 + Keyboard/Keyboard/ROW_1: U14.18, U14.20, U14.22, U14.24, U14.26, U14.28, U14.30, U14.32, U14.34, U14.36; also elsewhere on the board
/STM32 + Keyboard/Keyboard/ROW_2: U14.44, U14.46, U14.48, U14.50, U14.52, U14.54, U14.56, U14.58, U14.60, U14.62; also elsewhere on the board
/STM32 + Keyboard/Keyboard/ROW_3: U14.70, U14.72, U14.74, U14.76, U14.78, U14.80, U14.82, U14.84, U14.86, U14.88; also elsewhere on the board
/STM32 + Keyboard/Keyboard/ROW_4: U14.96, U14.98, U14.100, U14.102, U14.104, U14.106, U14.108, U14.110, U14.112, U14.114; also elsewhere on the board
/STM32 + Keyboard/Keyboard/ROW_5: U14.64, U14.66, U14.122, U14.124, U14.126, U14.128, U14.130, U14.132, U14.134, U14.136; also elsewhere on the board
/STM32 + Keyboard/Keyboard/ROW_6: U14.42, U14.90, U14.92, U14.94, U14.116, U14.118, U14.120, U14.138, U14.140, U14.142; also elsewhere on the board
/STM32 + Keyboard/Keyboard/ROW_7: SW11.2, SW12.2, SW13.2, SW14.2, SW15.2, SW16.2, SW17.2, SW18.2, SW19.2, U14.68; also elsewhere on the board

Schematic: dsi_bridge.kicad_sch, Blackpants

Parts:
C32: 10uF; C_0603_1608Metric; MPN CL10A106MA8NRNC
C44: 1uF; C_0402_1005Metric; MPN CL05B105KQ5NQNC
D13: 1N5819WS; D_SOD-323; MPN 1N5819WS
D15, D16, D17, D18, D19, D20, D21, D22: LED; LTW-010DCG; MPN LTW-010DCG
L3: 6.8uH; L_Vishay_IFSC-1515AH_4x4x1.8mm; MPN IFSC1515AHER6R8M01
R22: 100K; R_0402_1005Metric; MPN RC0402FR-13100KL
R23: 4R7; R_0402_1005Metric; MPN 0402WGF470KTCE
U15: AP3032; SOT-23-6_Handsoldering; MPN AP3032KTR-G1

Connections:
+5V: C32.1, L3.1, U15.6 (VIN); also elsewhere on the board
+13v: C44.1, D13.1 (K), D15.2 (A), D19.2 (A), U15.5 (OV)
/STM32 + Keyboard/BL_PWM: R22.1, U15.4 (CTRL); also elsewhere on the board
/STM32 + Keyboard/Keyboard Backlight/FB: D18.1 (K), D22.1 (K), R23.1, U15.3 (FB)
GND: C32.2, C44.2, R22.2, R23.2, U15.2 (GND); also elsewhere on the board
unnamed: D13.2 (A), L3.2, U15.1 (SW)
unnamed: D15.1 (K), D16.2 (A)
unnamed: D16.1 (K), D17.2 (A)
unnamed: D17.1 (K), D18.2 (A)
unnamed: D19.1 (K), D20.2 (A)
unnamed: D20.1 (K), D21.2 (A)
unnamed: D21.1 (K), D22.2 (A)

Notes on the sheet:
40mA @ 13v
Keeb backlight DC-DC
